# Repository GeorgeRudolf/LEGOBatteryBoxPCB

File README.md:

# LEGOBatteryBoxPCB
In case you were careless or just a victim of Duracells.

In my case, my younger self was not too careful with removing alkalines from Power Functions battery boxes (59510c01) when putting sets away. Sure, I can bodge the old PCB, in most cases, or buy a copycat battery box for next to nothing, but I felt like a replacement PCB for the originals would be good to have. I suspect this fits the earlier gray and red 9V box of the same style (54950c01) - haven't opened one to check.

Contacts: I have been using acid to clean the corrosion, and then nickel-plating them. All very easy to do, plenty of tutorials online.

This is a bit of a quick and dirty hack - which I felt should be enough for such a simple object. No improvement attempt was made - this is supposed to be a direct replacement, for which you should lift the parts from the old PCB.
The KiCad project files, ugly as they may be, are included, as well as Gerber files that you can use to get PCBs made directly at the boardhouse of your choice. Use 1mm thickness for the PCB. Select gold plating (ENIG) for best results. If you're in the US, OSHPark is probably the best choice here. Anywhere else depends on shipping.

I'd love to know if these end up being helpful to you.

Finally - these are being licensed as free for non-commercial use. Please do not resell for profit, or remove attribution.

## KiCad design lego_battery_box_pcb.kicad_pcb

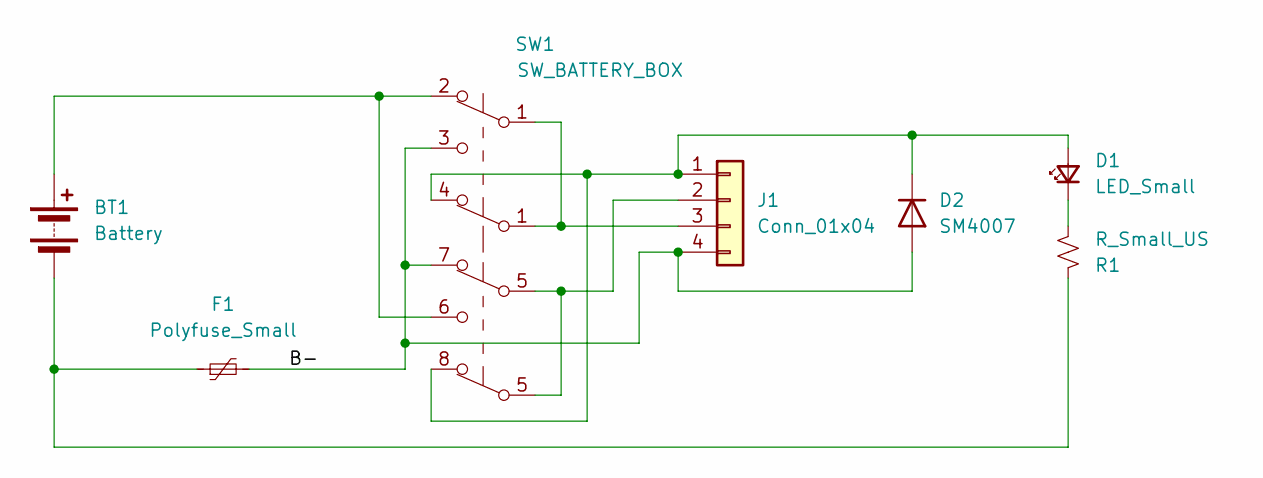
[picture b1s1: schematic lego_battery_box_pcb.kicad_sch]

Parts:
BT1: Battery; BATTERY
D1: LED_Small; LED_Rectangular_W3.0mm_H2.0mm
D2: SM4007; D_MELF
F1: Polyfuse_Small; Fuse_2512_6332Metric
J1: Conn_01x04; PinSocket_1x04_P1.27mm_Vertical
R1: R_Small_US; R_0603_1608Metric
SW1: SW_BATTERY_BOX; SWITCH

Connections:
/B-: D2.2 (A), F1.2, J1.4, SW1.3 (B-), SW1.7 (B-)
unnamed: BT1.1 (+), SW1.2 (B+), SW1.6 (B+)
unnamed: BT1.2 (-), F1.1, R1.1
unnamed: D1.2 (A), D2.1 (K), J1.1, SW1.4 (9V), SW1.8 (9V)
unnamed: D1.1 (K), R1.2
unnamed: J1.2, SW1.5 (M2)
unnamed: J1.3, SW1.1 (M1)

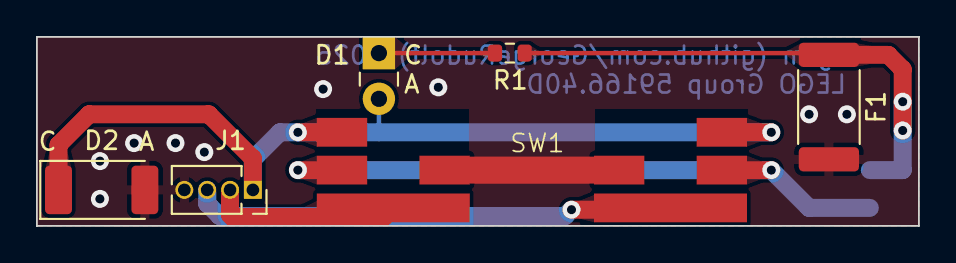
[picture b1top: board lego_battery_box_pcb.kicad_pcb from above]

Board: 2 copper layers, 49.0 x 10.5 mm, 7 parts (1 on the bottom side), 7 nets.

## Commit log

2025-02-09 adding project files
2025-02-09 Update README.md
    Messed up and forgot to state PCB thickness.
